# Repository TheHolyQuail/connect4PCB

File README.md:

# connect4PCB
Connect 4 on a PCB

Uses an ATTINY 45 to read button presses and control a grid of WS2813 LEDs.
Runs a game of connect 4 complete with auto win detecction.

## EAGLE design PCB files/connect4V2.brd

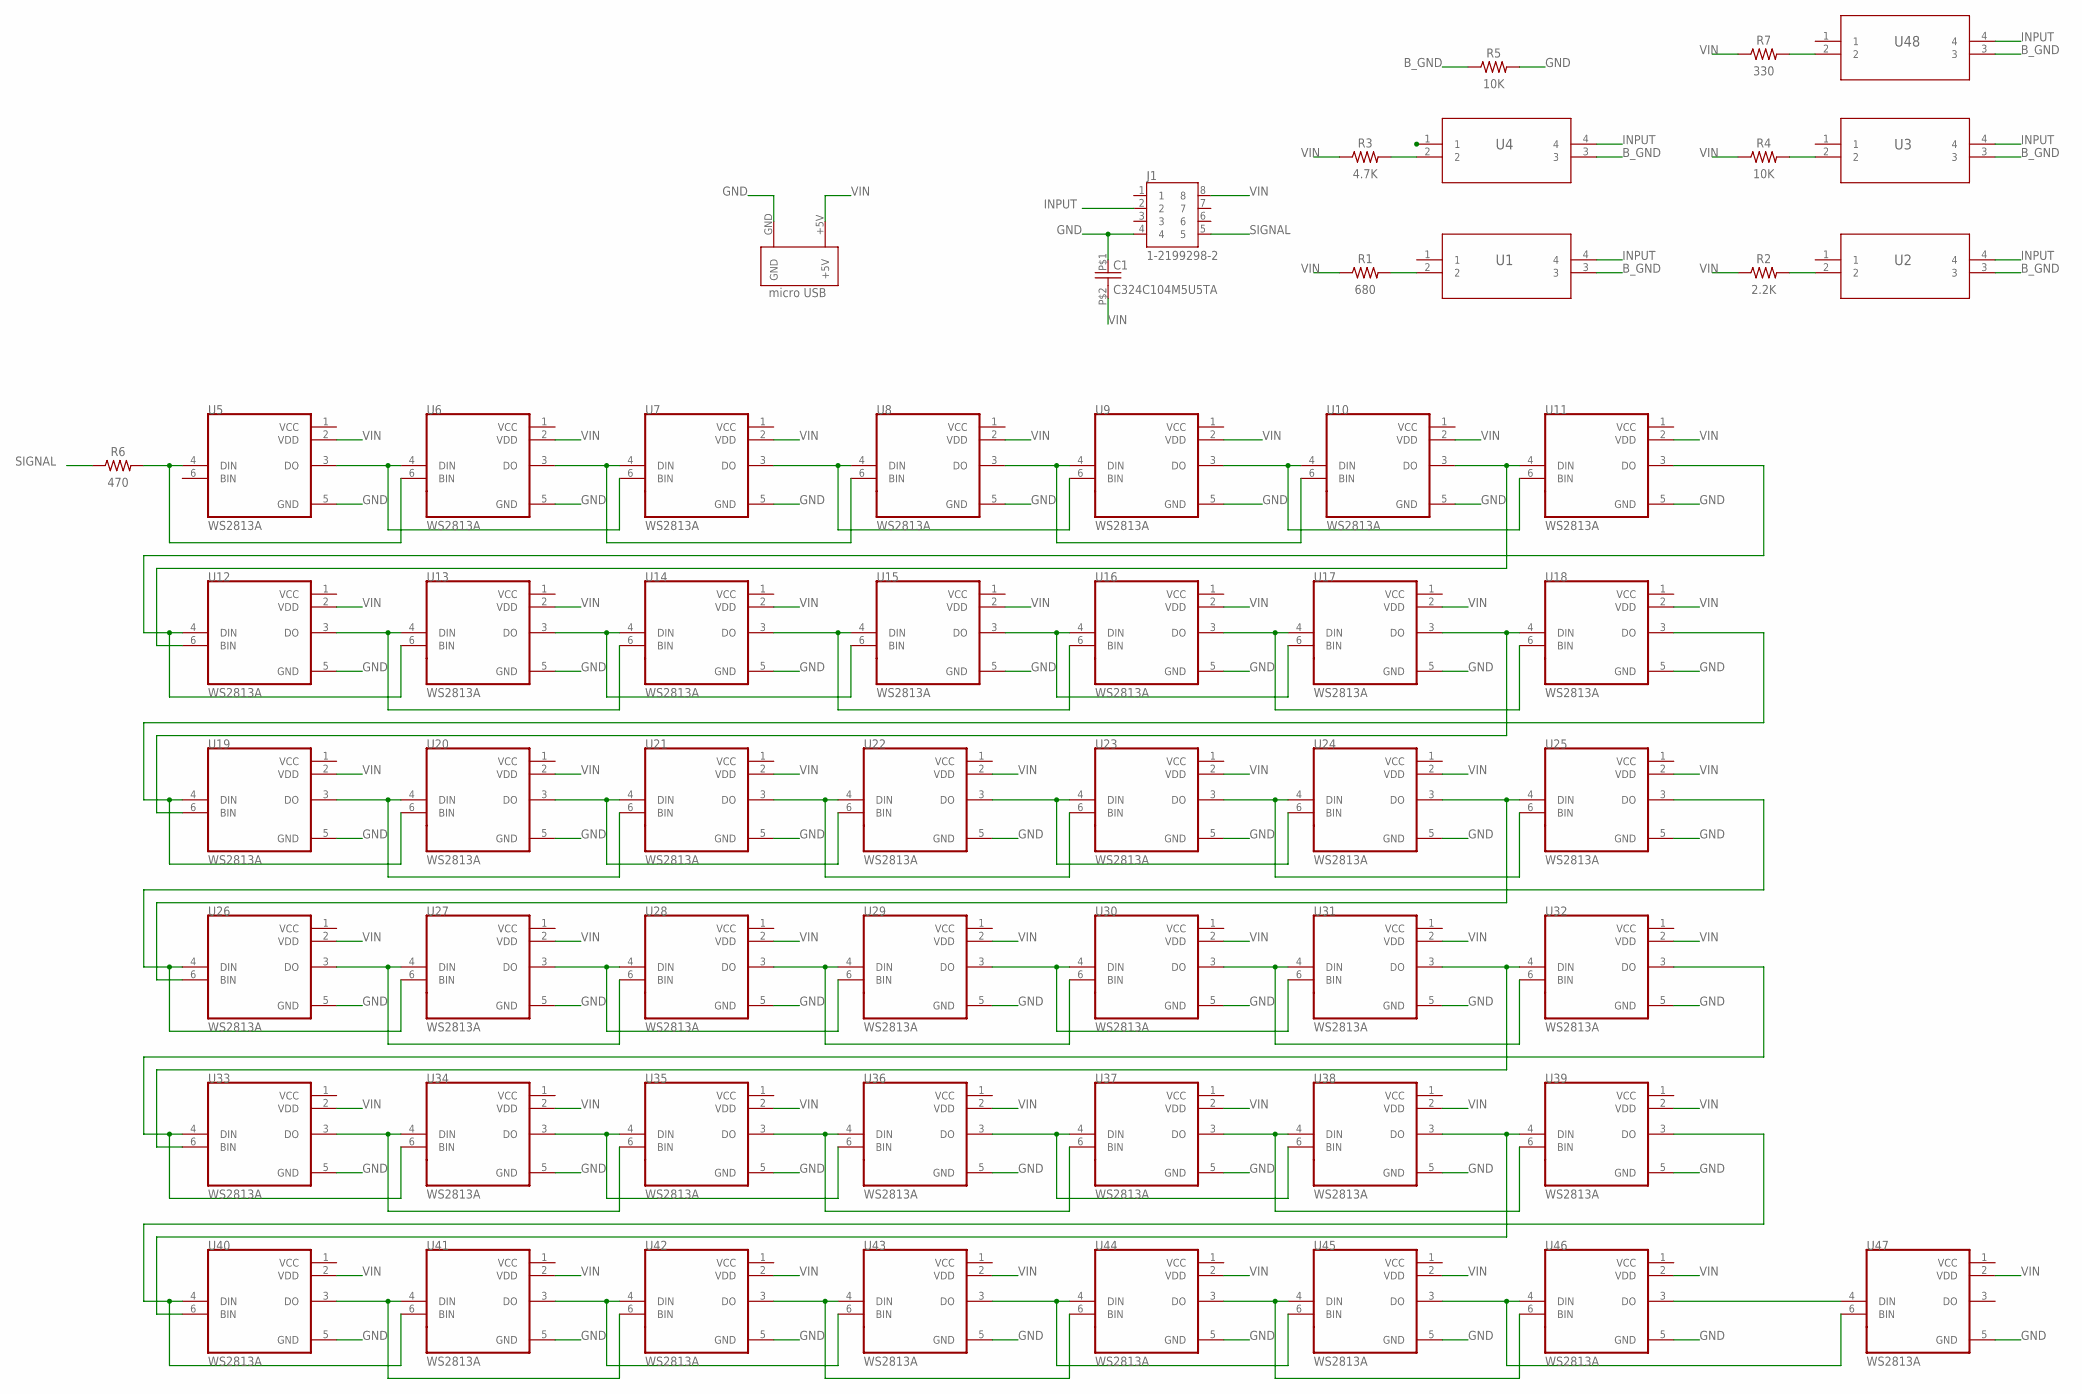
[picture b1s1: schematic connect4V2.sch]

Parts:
C1: C324C104M5U5TA; CAPRR254W55L508T318H508P
J1: 1-2199298-2; TE_1-2199298-2
R1: 680; RESAD724W46L381D178B
R2: 2.2K; RESAD724W46L381D178B
R3: 4.7K; RESAD724W46L381D178B
R4, R5: 10K; RESAD724W46L381D178B
R6: 470; RESAD724W46L381D178B
R7: 330; RESAD724W46L381D178B
U1, U2, U3, U4, U48: PTS526_SK15_SMTR2_LFSSMT_FS-M; SMT_FS-M
U5, U6, U7, U8, U9, U10, U11, U12, U13, U14, U15, U16, U17, U18, U19, U20, U21, U22, U23, U24, U25, U26, U27, U28, U29, U30, U31, U32, U33, U34, U35, U36, U37, U38, U39, U40, U41, U42, U43, U44, U45, U46, U47: WS2813A; LED_WS2813A
U$1: MICROUSB-5P-FEMALE-AB

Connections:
B_GND: R5.1, U1.3, U2.3, U3.3, U4.3, U48.3
GND: C1.P$1 (1), J1.4, R5.2, U5.5 (GND), U6.5 (GND), U7.5 (GND), U8.5 (GND), U9.5 (GND), U10.5 (GND), U11.5 (GND), U12.5 (GND), U13.5 (GND), U14.5 (GND), U15.5 (GND), U16.5 (GND), U17.5 (GND), U18.5 (GND), U19.5 (GND), U20.5 (GND), U21.5 (GND), U22.5 (GND), U23.5 (GND), U24.5 (GND), U25.5 (GND), U26.5 (GND), U27.5 (GND), U28.5 (GND), U29.5 (GND), U30.5 (GND), U31.5 (GND), U32.5 (GND), U33.5 (GND), U34.5 (GND), U35.5 (GND), U36.5 (GND), U37.5 (GND), U38.5 (GND), U39.5 (GND), U40.5 (GND), U41.5 (GND), U42.5 (GND), U43.5 (GND), U44.5 (GND), U45.5 (GND), U46.5 (GND), U47.5 (GND), U$1.GND
INPUT: J1.2, U1.4, U2.4, U3.4, U4.4, U48.4
unnamed: U6.3 (DO), U7.4 (DIN), U8.6 (BIN)
unnamed: U5.3 (DO), U6.4 (DIN), U7.6 (BIN)
unnamed: U7.3 (DO), U8.4 (DIN), U9.6 (BIN)
unnamed: U8.3 (DO), U9.4 (DIN), U10.6 (BIN)
unnamed: U10.3 (DO), U11.4 (DIN), U12.6 (BIN)
unnamed: U13.3 (DO), U14.4 (DIN), U15.6 (BIN)
unnamed: U30.3 (DO), U31.4 (DIN), U32.6 (BIN)
unnamed: U12.3 (DO), U13.4 (DIN), U14.6 (BIN)
unnamed: U14.3 (DO), U15.4 (DIN), U16.6 (BIN)
unnamed: U15.3 (DO), U16.4 (DIN), U17.6 (BIN)
unnamed: U16.3 (DO), U17.4 (DIN), U18.6 (BIN)
unnamed: U17.3 (DO), U18.4 (DIN), U19.6 (BIN)
unnamed: U19.3 (DO), U20.4 (DIN), U21.6 (BIN)
unnamed: U20.3 (DO), U21.4 (DIN), U22.6 (BIN)
unnamed: U21.3 (DO), U22.4 (DIN), U23.6 (BIN)
unnamed: U22.3 (DO), U23.4 (DIN), U24.6 (BIN)
unnamed: U23.3 (DO), U24.4 (DIN), U25.6 (BIN)
unnamed: U24.3 (DO), U25.4 (DIN), U26.6 (BIN)
unnamed: U18.3 (DO), U19.4 (DIN), U20.6 (BIN)
unnamed: U26.3 (DO), U27.4 (DIN), U28.6 (BIN)
unnamed: U27.3 (DO), U28.4 (DIN), U29.6 (BIN)
unnamed: U28.3 (DO), U29.4 (DIN), U30.6 (BIN)
unnamed: U29.3 (DO), U30.4 (DIN), U31.6 (BIN)
unnamed: U31.3 (DO), U32.4 (DIN), U33.6 (BIN)
unnamed: U25.3 (DO), U26.4 (DIN), U27.6 (BIN)
unnamed: U33.3 (DO), U34.4 (DIN), U35.6 (BIN)
unnamed: U34.3 (DO), U35.4 (DIN), U36.6 (BIN)
unnamed: U35.3 (DO), U36.4 (DIN), U37.6 (BIN)
unnamed: U36.3 (DO), U37.4 (DIN), U38.6 (BIN)
unnamed: U37.3 (DO), U38.4 (DIN), U39.6 (BIN)
unnamed: U38.3 (DO), U39.4 (DIN), U40.6 (BIN)
unnamed: U32.3 (DO), U33.4 (DIN), U34.6 (BIN)
unnamed: U40.3 (DO), U41.4 (DIN), U42.6 (BIN)
unnamed: U41.3 (DO), U42.4 (DIN), U43.6 (BIN)
unnamed: U42.3 (DO), U43.4 (DIN), U44.6 (BIN)
unnamed: U11.3 (DO), U12.4 (DIN), U13.6 (BIN)
unnamed: U43.3 (DO), U44.4 (DIN), U45.6 (BIN)
unnamed: U44.3 (DO), U45.4 (DIN), U46.6 (BIN)
unnamed: U45.3 (DO), U46.4 (DIN), U47.6 (BIN)
unnamed: U39.3 (DO), U40.4 (DIN), U41.6 (BIN)
unnamed: U46.3 (DO), U47.4 (DIN)
unnamed: R1.2, U1.2
unnamed: R3.2, U4.2
unnamed: R2.2, U2.2
unnamed: R4.2, U3.2
unnamed: U9.3 (DO), U10.4 (DIN), U11.6 (BIN)
unnamed: R7.2, U48.2
unnamed: R6.2, U5.4 (DIN), U6.6 (BIN)
SIGNAL: J1.5, R6.1
VCC: U5.1 (VCC), U6.1 (VCC), U7.1 (VCC), U8.1 (VCC), U9.1 (VCC), U10.1 (VCC), U11.1 (VCC), U12.1 (VCC), U13.1 (VCC), U14.1 (VCC), U15.1 (VCC), U16.1 (VCC), U17.1 (VCC), U18.1 (VCC), U19.1 (VCC), U20.1 (VCC), U21.1 (VCC), U22.1 (VCC), U23.1 (VCC), U24.1 (VCC), U25.1 (VCC), U26.1 (VCC), U27.1 (VCC), U28.1 (VCC), U29.1 (VCC), U30.1 (VCC), U31.1 (VCC), U32.1 (VCC), U33.1 (VCC), U34.1 (VCC), U35.1 (VCC), U36.1 (VCC), U37.1 (VCC), U38.1 (VCC), U39.1 (VCC), U40.1 (VCC), U41.1 (VCC), U42.1 (VCC), U43.1 (VCC), U44.1 (VCC), U45.1 (VCC), U46.1 (VCC), U47.1 (VCC)
VIN: C1.P$2 (2), J1.8, R1.1, R2.1, R3.1, R4.1, R7.1, U5.2 (VDD), U6.2 (VDD), U7.2 (VDD), U8.2 (VDD), U9.2 (VDD), U10.2 (VDD), U11.2 (VDD), U12.2 (VDD), U13.2 (VDD), U14.2 (VDD), U15.2 (VDD), U16.2 (VDD), U17.2 (VDD), U18.2 (VDD), U19.2 (VDD), U20.2 (VDD), U21.2 (VDD), U22.2 (VDD), U23.2 (VDD), U24.2 (VDD), U25.2 (VDD), U26.2 (VDD), U27.2 (VDD), U28.2 (VDD), U29.2 (VDD), U30.2 (VDD), U31.2 (VDD), U32.2 (VDD), U33.2 (VDD), U34.2 (VDD), U35.2 (VDD), U36.2 (VDD), U37.2 (VDD), U38.2 (VDD), U39.2 (VDD), U40.2 (VDD), U41.2 (VDD), U42.2 (VDD), U43.2 (VDD), U44.2 (VDD), U45.2 (VDD), U46.2 (VDD), U47.2 (VDD), U$1.+5V

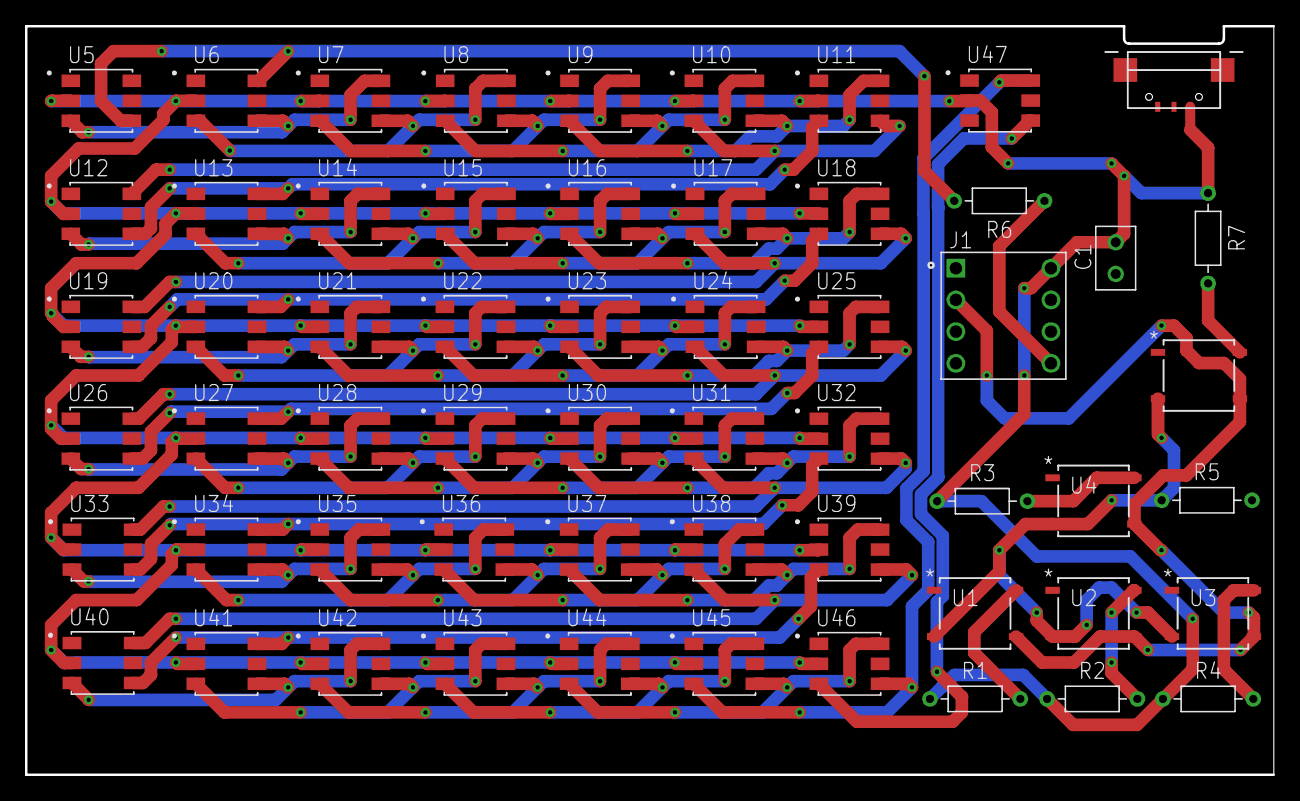
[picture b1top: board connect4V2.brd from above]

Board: 2 copper layers, 100.0 x 60.0 mm, 58 parts (0 on the bottom side), 54 nets.

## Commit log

2021-06-16 Add some libraries
2021-06-22 Add PCB v1 files
2021-07-11 Add PCB v2 files including updated WS2813 library
2021-07-25 Add updated EDA files and code with button and LED color change functionality.
2021-07-25 Fix array for game values.
2021-07-27 remove delay reliant button detection and set up infrastructure to start making the game
2021-07-27 seperate display updates from button actions
2021-07-27 Add game array to LED display conversion
2021-07-27 Add piece plaing functionality
2021-07-27 Improve haning piece representation and fix top piece overwrite bug
2021-07-27 Add hanging piece skip over full columns function
2021-07-28 Change backgorund to blank to improve clarity of game
2021-07-28 Swap blue to yellow to mimic the original game.
2021-07-29 Remove unecessary libraries.
2021-07-29 Remove unecessary test function
2021-07-29 Polish the code by removing commented out code and fixing an unintended haning LED movement function naming conflict.

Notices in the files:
parts and their libraries:
COPYRIGHT: Copyright (C) 2018 Accelerated Designs. All rights reserved
